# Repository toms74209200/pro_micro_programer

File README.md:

# pro_micro_programmer
Arduino ISCP board for Pro micro

## License

MIT License

## Author

[toms74209200](<https://github.com/toms74209200>)

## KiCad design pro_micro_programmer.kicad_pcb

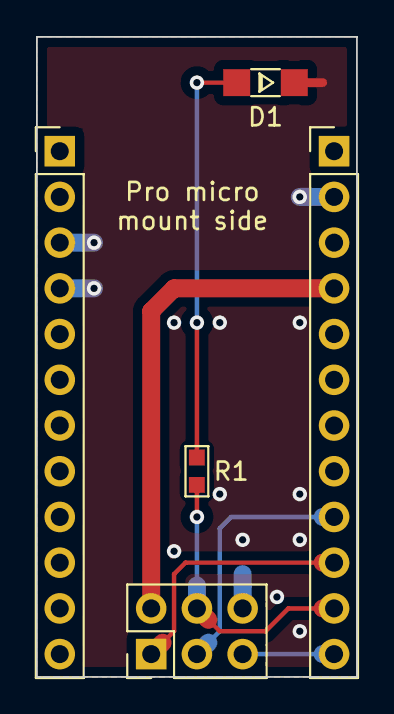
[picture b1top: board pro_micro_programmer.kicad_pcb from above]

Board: 2 copper layers, 17.8 x 35.6 mm, 5 parts (0 on the bottom side), 7 nets.

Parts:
D1: Rohm SML-E1 LED; LED-1206
J1, J2: Conn_01x12; PinHeader_1x12_P2.54mm_Vertical
J3: Conn_02x03; PinHeader_2x03_P2.54mm_Vertical
R1: 10k; R0603

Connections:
/MISO: J2.10, J3.1
/MOSI: J2.11, J3.4, R1.1
/RESET: J2.12, J3.5
/SCLK: J2.9, J3.3
GND: D1.1, J1.3, J1.4, J2.2, J3.6
unnamed: D1.2, R1.2
VCC: J2.4, J3.2

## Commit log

2021-01-31 [add]add first
2021-01-31 [docs]add README
2021-02-01 [docs]fix typo
2021-02-01 [add]add logo
2021-02-02 [add]add panelize
2021-03-01 [add]add silk
